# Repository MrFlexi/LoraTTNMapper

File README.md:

# LoraTTNMapper
Lora TTN Mapper

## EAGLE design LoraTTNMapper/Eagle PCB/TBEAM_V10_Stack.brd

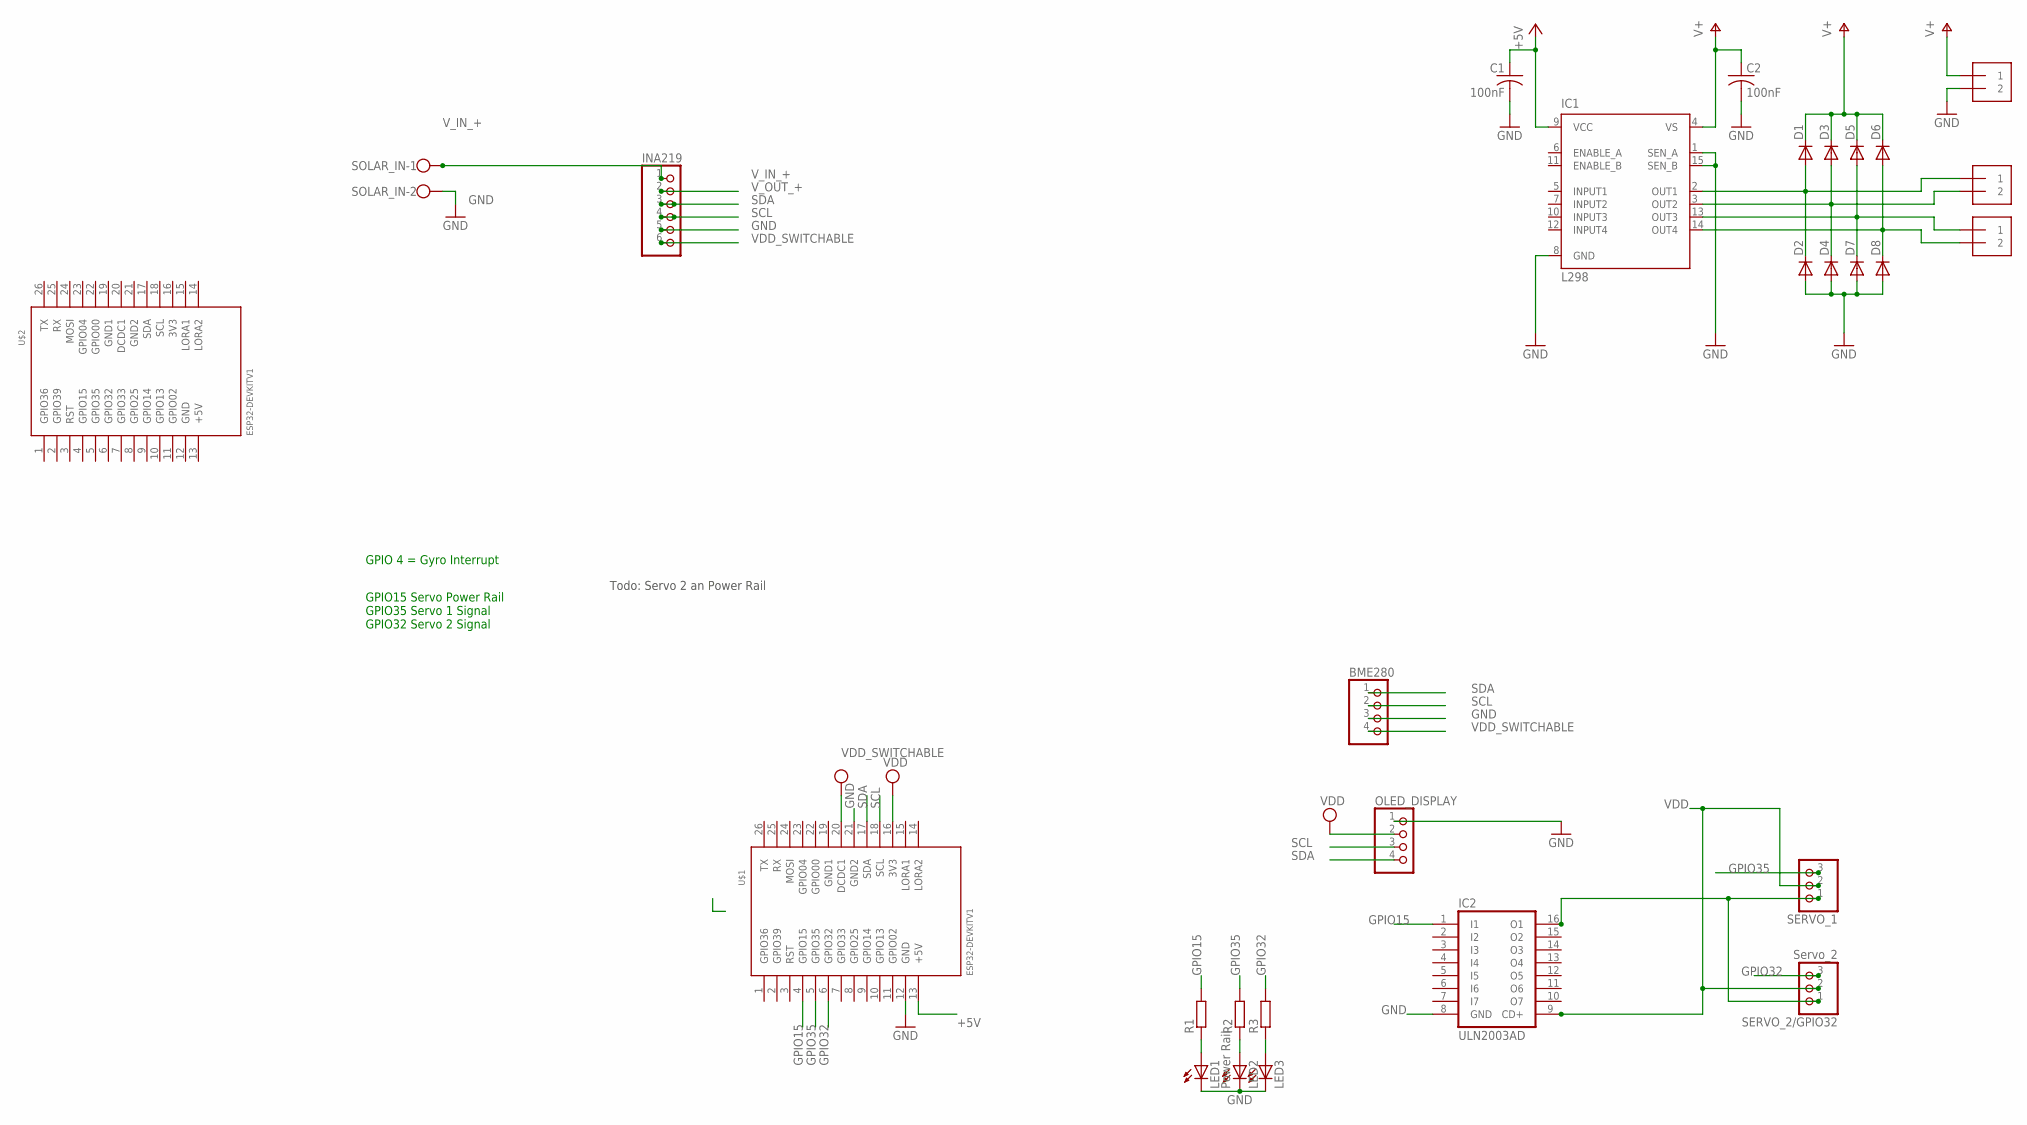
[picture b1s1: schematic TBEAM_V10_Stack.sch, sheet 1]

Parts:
BME280: PINHD-1X4; 1X04
C1, C2: 100nF; C050-024X044
D1, D2, D3, D4, D5, D6, D7, D8: DIODE-D-5; D-5
IC1: L298; MULTIWATT-15
IC2: ULN2003AD; SO16
INA219: PINHD-1X6; 1X06
J1, J2, J3: 1X2-3.5MM
LED1: Power Rail; SML1206
LED2, LED3: LEDSML1206; SML1206
OLED_DISPLAY: PINHD-1X4; 1X04
R1, R2, R3: R-EU_R1206; R1206
SERVO_1: PINHD-1X3; 1X03
SERVO_2/GPIO32: Servo_2; 1X03
SOLAR_IN: W237-102
U$1, U$2: ESP32DEVKITV1; ESP32-DEVKITV1

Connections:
+5V: C1.1, IC1.9 (VCC), U$1.13 (+5V)
GND: BME280.3, C1.2, C2.2, D2.A, D4.A, D7.A, D8.A, IC1.1 (SEN_A), IC1.8 (GND), IC1.15 (SEN_B), IC2.8 (GND), INA219.5, J1.2, LED1.C, LED2.C, LED3.C, OLED_DISPLAY.1, SOLAR_IN.2, U$1.12 (GND), U$1.21 (GND2)
GPIO15: IC2.1 (I1), R1.2, U$1.4 (GPIO15)
GPIO32: R3.2, SERVO_2/GPIO32.3, U$1.6 (GPIO32)
GPIO35: R2.2, SERVO_1.3, U$1.5 (GPIO35)
unnamed: IC2.16 (O1), SERVO_1.1, SERVO_2/GPIO32.1
unnamed: LED1.A, R1.1
unnamed: LED2.A, R2.1
unnamed: LED3.A, R3.1
unnamed: D1.A, D2.C, IC1.2 (OUT1), J2.1
unnamed: D3.A, D4.C, IC1.3 (OUT2), J2.2
unnamed: D6.A, D8.C, IC1.14 (OUT4), J3.2
unnamed: D5.A, D7.C, IC1.13 (OUT3), J3.1
SCL: BME280.2, INA219.4, OLED_DISPLAY.3, U$1.18 (SCL)
SDA: BME280.1, INA219.3, OLED_DISPLAY.4, U$1.17 (SDA)
V+: C2.1, D1.C, D3.C, D5.C, D6.C, IC1.4 (VS), J1.1
VDD: IC2.9 (CD+), OLED_DISPLAY.2, SERVO_1.2, SERVO_2/GPIO32.2, U$1.16 (3V3)
VDD_SWITCHABLE: BME280.4, INA219.6, U$1.20 (DCDC1)
V_IN_+: INA219.1, SOLAR_IN.1
V_OUT_+: INA219.2

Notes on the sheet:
GPIO15 Servo Power Rail GPIO35 Servo 1 Signal GPIO32 Servo 2 Signal
GPIO 4 = Gyro Interrupt
Todo: Servo 2 an Power Rail

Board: 2 copper layers, 29 parts (0 on the bottom side), 19 nets, no tracks yet.

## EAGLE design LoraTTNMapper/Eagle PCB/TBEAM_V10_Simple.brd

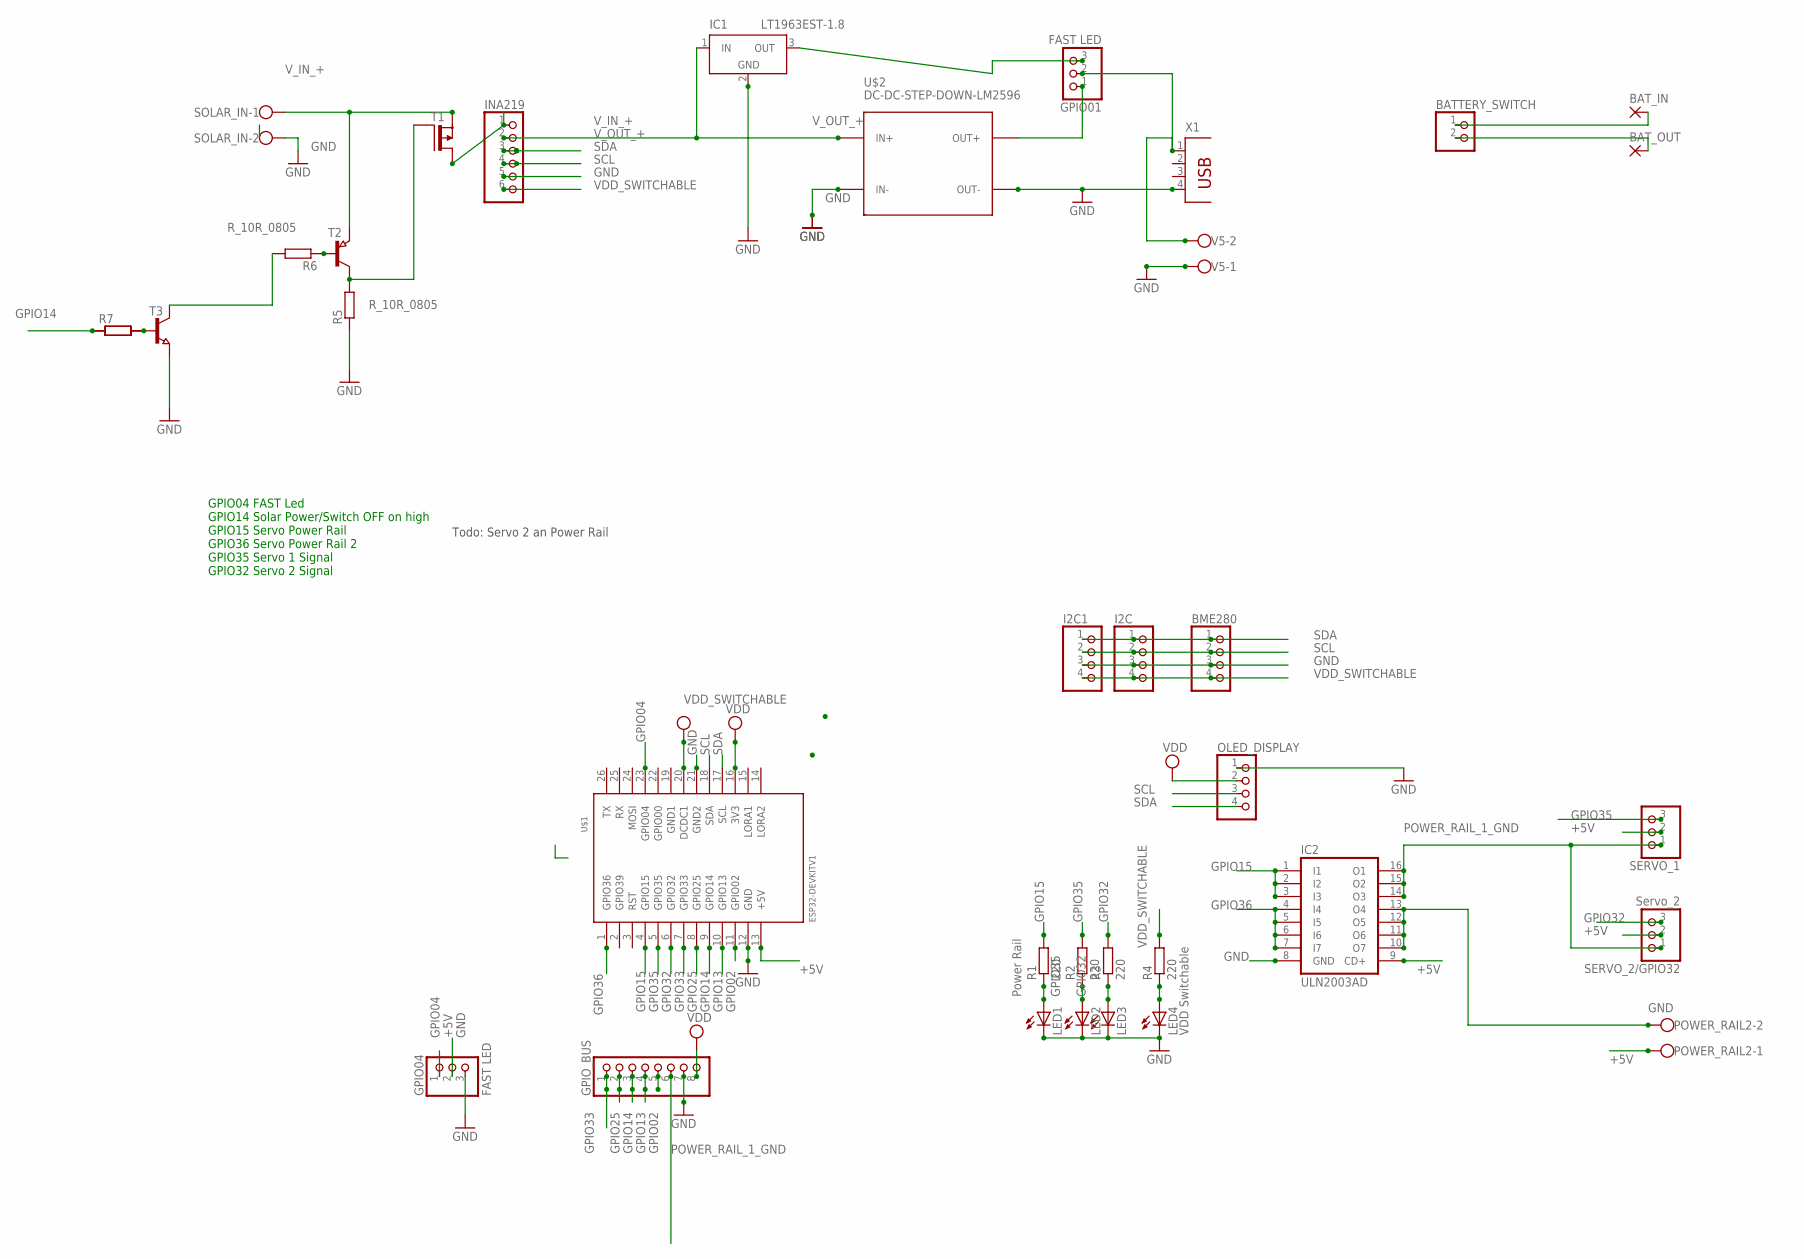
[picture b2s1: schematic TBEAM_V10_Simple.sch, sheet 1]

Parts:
BATTERY_SWITCH: PINHD-1X2; 1X02
BAT_IN: SMD5; SMD2,54-5,08
BAT_OUT: SMD5; SMD2,54-5,08
BME280: PINHD-1X4; 1X04
GPIO01, GPIO04: FAST LED; 1X03
GPIO_BUS: PINHD-1X8; 1X08
I2C, I2C1: PINHD-1X4; 1X04
IC1: LT1963EST-1.8; SOT223
IC2: ULN2003AD; SO16
INA219: PINHD-1X6; 1X06
LED1: Power Rail; SML1206
LED2: GPIO35; SML1206
LED3: GPIO32; SML1206
LED4: VDD Switchable; SML1206
OLED_DISPLAY: PINHD-1X4; 1X04
POWER_RAIL2: W237-102
R1, R2, R3, R4: 220; R1206
R5, R6: R_10R_0805; R0805
R7, R8: R_1.8K_0805; R0805
SERVO_1: PINHD-1X3; 1X03
SERVO_2/GPIO32: Servo_2; 1X03
SOLAR_IN: W237-102
T1: T_P-MOSFET_AO3401A_ALPHA_SOT23-GSD; SOT23
T2: T_PNP_SS8550-Y2_CHANGJ_SOT23-BEC; SOT23
T3: T_NPN_SS8050_CHANGJ_SOT23-BEC; SOT23
U$1: ESP32DEVKITV1; ESP32-DEVKITV1
U$2: DC-DC-STEP-DOWN-LM2596
V5: W237-102
X1: PN87520

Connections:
+5V: GPIO04.2, IC2.9 (CD+), POWER_RAIL2.1, SERVO_1.2, SERVO_2/GPIO32.2, U$1.13 (+5V)
BUCK-CONVERTER: GPIO01.1, U$2.OUT+
GND: BME280.3, GPIO04.3, GPIO_BUS.7, I2C.3, I2C1.3, IC1.2 (GND), IC1.4 (GND), IC2.8 (GND), INA219.5, LED1.C, LED2.C, LED3.C, LED4.C, OLED_DISPLAY.1, R5.1, SOLAR_IN.2, T3.2 (E), U$1.12 (GND), U$1.21 (GND2), U$2.IN-, U$2.OUT-, V5.1, X1.4
GPIO02: GPIO_BUS.5, U$1.11 (GPIO02)
GPIO04: GPIO04.1, U$1.23 (GPIO04)
GPIO13: GPIO_BUS.4, U$1.10 (GPIO13)
GPIO14: GPIO_BUS.3, R7.1, R8.1, U$1.9 (GPIO14)
GPIO15: IC2.1 (I1), IC2.2 (I2), IC2.3 (I3), R1.2, U$1.4 (GPIO15)
GPIO25: GPIO_BUS.2, U$1.8 (GPIO25)
GPIO32: R3.2, SERVO_2/GPIO32.3, U$1.6 (GPIO32)
GPIO33: GPIO_BUS.1, U$1.7 (GPIO33)
GPIO35: R2.2, SERVO_1.3, U$1.5 (GPIO35)
GPIO36: IC2.4 (I4), IC2.5 (I5), IC2.6 (I6), IC2.7 (I7), U$1.1 (GPIO36)
unnamed: LED1.A, R1.1
unnamed: LED2.A, R2.1
unnamed: LED3.A, R3.1
unnamed: GPIO01.2, V5.2, X1.1
unnamed: BATTERY_SWITCH.1, BAT_IN.1
unnamed: BATTERY_SWITCH.2, BAT_OUT.1
unnamed: LED4.A, R4.1
unnamed: IC2.10 (O7), IC2.11 (O6), IC2.12 (O5), IC2.13 (O4), POWER_RAIL2.2
unnamed: SOLAR_IN.1, T1.2 (S), T2.2 (E)
unnamed: GPIO01.3, IC1.3 (OUT)
unnamed: R5.2, T1.1 (G), T2.3 (C)
unnamed: R6.1, T2.1 (B)
unnamed: R6.2, T3.3 (C)
unnamed: R7.2, R8.2, T3.1 (B)
POWER_RAIL_1_GND: GPIO_BUS.6, IC2.14 (O3), IC2.15 (O2), IC2.16 (O1), SERVO_1.1, SERVO_2/GPIO32.1
SCL: BME280.2, I2C.2, I2C1.2, INA219.4, OLED_DISPLAY.3, U$1.18 (SDA)
SDA: BME280.1, I2C.1, I2C1.1, INA219.3, OLED_DISPLAY.4, U$1.17 (SCL)
VDD: GPIO_BUS.8, OLED_DISPLAY.2, U$1.16 (3V3)
VDD_SWITCHABLE: BME280.4, I2C.4, I2C1.4, INA219.6, R4.2, U$1.20 (DCDC1)
V_IN_+: INA219.1, T1.3 (D)
V_OUT_+: IC1.1 (IN), INA219.2, U$2.IN+

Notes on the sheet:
GPIO04 FAST Led GPIO14 Solar Power/Switch OFF on high GPIO15 Servo Power Rail GPIO36 Servo Power Rail 2 GPIO35 Servo 1 Signal GPIO32 Servo 2 Signal
Todo: Servo 2 an Power Rail

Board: 2 copper layers, 36 parts (3 on the bottom side), 34 nets, no tracks yet.

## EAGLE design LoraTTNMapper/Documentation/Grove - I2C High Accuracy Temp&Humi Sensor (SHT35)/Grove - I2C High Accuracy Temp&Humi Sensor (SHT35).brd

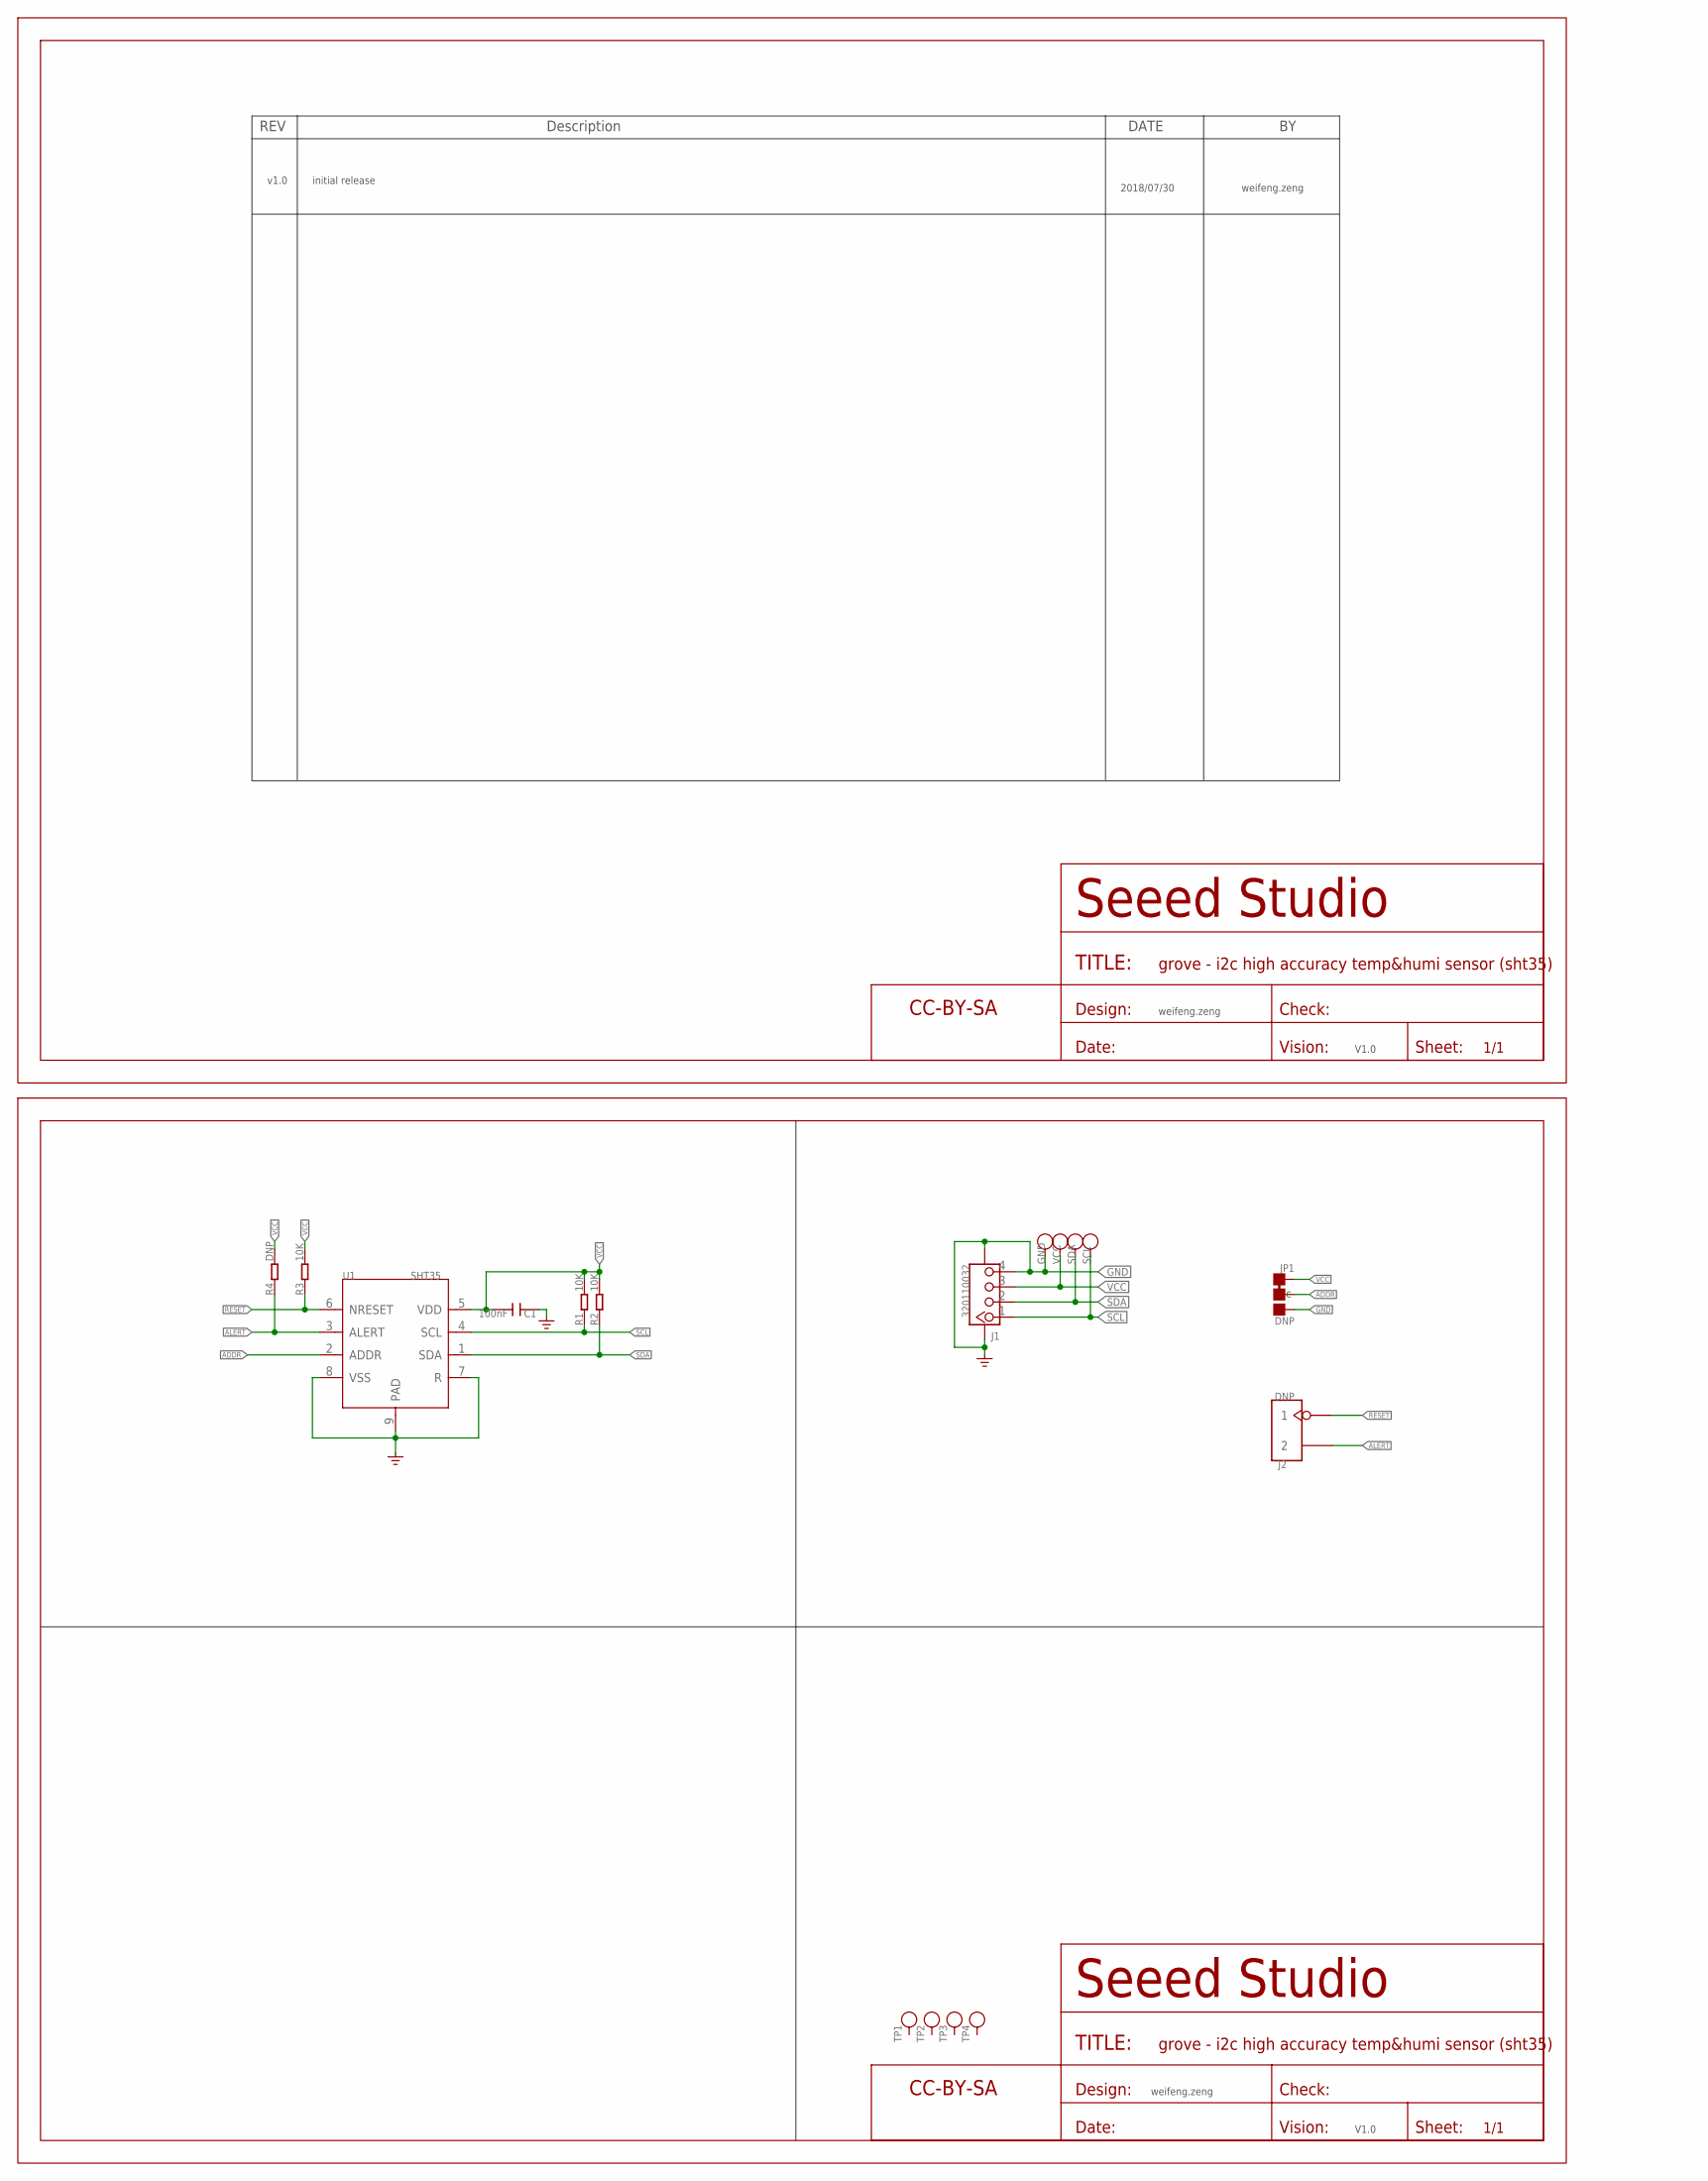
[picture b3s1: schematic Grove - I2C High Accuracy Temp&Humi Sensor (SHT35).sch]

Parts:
C1: 100nF; C0603
FR1, FR2: SEEEDSTUDIO-OPEN-SCH-FRAME; SEEEDSTUDIO-PCB-FRAME
GND: TEST-POINT'4545'; TP-D45MIL
J1: 320110032; HW4-SMD-2.0-90D
J2: DNP; H2-2.54
JP1: DNP; 3P-SMD-SHORT
R1, R2, R3: 10K; R0603
R4: DNP; R0603
SCL: TEST-POINT'4545'; TP-D45MIL
SDA: TEST-POINT'4545'; TP-D45MIL
TP1, TP2, TP3, TP4: TEST-POINT'4545'; TP-D45MIL
U1: SHT35; DFN8-0.5-2.5X2.5MM
VCC: TEST-POINT'4545'; TP-D45MIL

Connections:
ADDR: JP1.MM (C), U1.2 (ADDR)
ALERT: J2.2, R4.1, U1.3 (ALERT)
GND: C1.2, GND.T, J1.4, J1.SS1, J1.SS2, JP1.00 (R), U1.7 (R), U1.8 (VSS), U1.9 (PAD)
RESET: J2.1, R3.1, U1.6 (NRESET)
SCL: J1.1, R1.1, SCL.T, U1.4 (SCL)
SDA: J1.2, R2.1, SDA.T, U1.1 (SDA)
VCC: C1.1, J1.3, JP1.11 (L), R1.2, R2.2, R3.2, R4.2, U1.5 (VDD), VCC.T

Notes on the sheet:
v1.0
initial release
2018/07/30
weifeng.zeng
V1.0

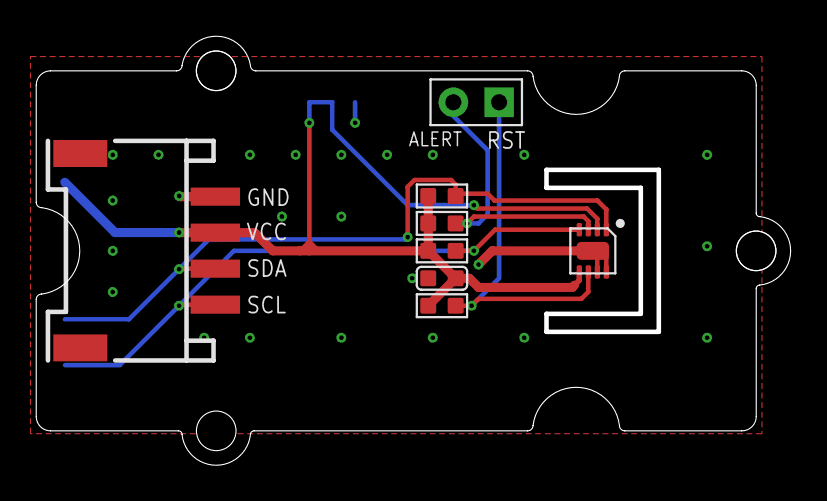
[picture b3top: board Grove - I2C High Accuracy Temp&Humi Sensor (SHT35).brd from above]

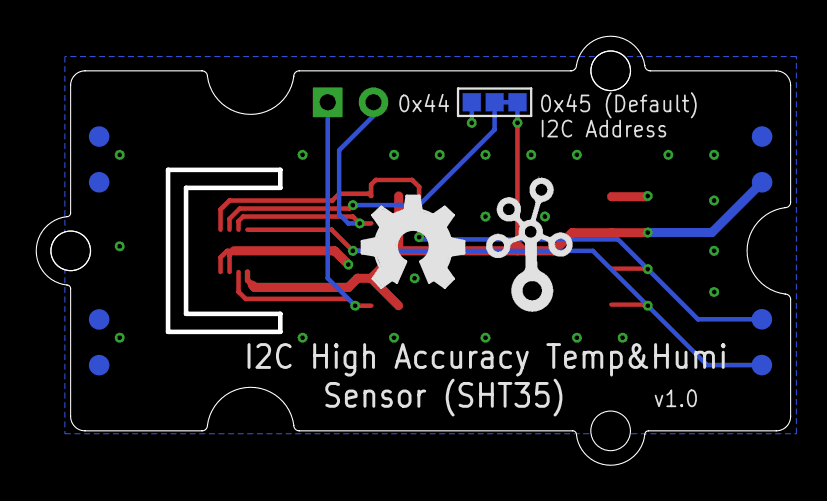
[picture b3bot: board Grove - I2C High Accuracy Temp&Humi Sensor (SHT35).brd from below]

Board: 2 copper layers, 41.9 x 23.8 mm, 22 parts (11 on the bottom side), 7 nets.

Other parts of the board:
U10: GROVE-TEST-PLATFORM
U$3: OSHW_FILLX200_NOTEXT
U$4: TWIGLOGO

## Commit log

2019-09-01 Init
2019-09-01 kein Display
2019-09-02 New TTN App
2019-09-06 T-Beam V1.0 with Power Managament Unit burned after unknown issue
2019-09-06 T-Beam Schematics and APX192 Datasheet added
2019-09-10 code sanitation
2019-09-11 code sanitation II
2019-09-11 Data Buffer included
2019-09-12 Now it compiles...
2019-09-12 Version 1.0
2019-09-12 Data Inbound
2019-09-12 Timing to be updated
2019-09-12 Power Management Includes copied
2019-09-12 Battery measurement included
2019-09-16 Display and deep sleep
2019-09-21 GPS low power mode
2019-09-25 Dashboard
2019-10-04 MQTT Included
2019-10-20 Compiles, but display errors AXP not O.K
2019-10-20 fast fertig
2019-10-21 Jipiii
2019-10-23 GPS code cleanup
2019-10-23 5 Min Deep Sleep
2019-10-23 Soft sleep / always on
2019-10-27 SolarPanel
2019-10-29 Message Queue In o.k.
2019-11-07 Button to switch display
2019-11-09 Lora send queue
2019-11-10 no gps fix
2019-11-11 Integration LPP Cayenne
2019-11-11 na ja
2019-11-12 GPS reset deleted
2019-11-12 BAT Voltage
2019-11-12 MQTT code cleanup
2019-11-14 lora.h
2019-11-14 lora h end
2019-11-14 Lora GPS
2019-11-14 GPS to Cayenne
2019-11-14 comments added
2019-11-16 LPP GPS fixed
2019-11-17 Queue Bug Fixig
2019-11-17 dodeel
2019-11-18 Improved queue handling
2019-11-18 Queue cleansing
2019-11-20 OTA Update
2019-11-20 OTA now its o.k.
2019-11-20 success
2019-11-21 Replace Ug2 lib by ss_oled
2019-11-21 DeepSleep ON
2019-11-23 all on
2019-11-23 V2.0
2019-11-23 jetzt klappt es
2019-11-25 ssisi
2019-11-25 Wifi Conditional off
2019-11-25 WIFI Optimization
2019-11-25 V2.3
2019-11-25 Display Update
2019-11-26 5 to 5
2019-11-26 LORA Firmware Version
2019-12-02 Sleep Off 2.6
2019-12-05 BLE Support
2019-12-05 BLE, no memory
2019-12-05 BLE OFF
2019-12-05 Flash Partition changed, minimal SPIFF
2019-12-06 Display Page Settings
2019-12-06 es geht
2019-12-18 Downgrade TBEAM V07
2019-12-18 down again
2019-12-18 down ok
2019-12-19 down
2019-12-19 some fixes in OTA
2019-12-19 micro spiffs
2019-12-19 more info
2019-12-19 tata
2019-12-20 displa defect
2019-12-25 Display Runmode = 0
2019-12-25 new start
2019-12-30 Downgrade V07 + Display O.K.
2019-12-30 Displav move O.K.
2020-01-08 Mini Spiff
2020-01-08 Min Spiff
2020-01-08 SOme enhancements V4.0
2020-01-08 small enhancement
2020-01-08 V1.0 Init
2020-01-08 Power On/Off Button
2020-01-08 Sleep On, OTA On
2020-01-08 30 Min Sleep
2020-01-09 minimal adjustments
2020-01-11 Deep Sleep / Power IRQ
2020-01-12 ADXL345
2020-01-13 ADXL burst read
2020-01-13 ADXL Event
2020-01-14 ADXL dump
2020-01-14 IRQ changes
2020-01-17 desplay error
2020-01-20 Display O.K.
2020-01-20 Dislay OK
2020-01-20 delays in startup routine --> no dumps
2020-01-22 RX Data: RSSi und RSI im Display
2020-01-22 Serial BT
2020-01-23 BLE Included
2020-01-23 2 BLE Services
2020-01-23 Bluethooth on
2020-01-23 docu
2020-01-25 Improvements
2020-01-26 GPIO 00 Interrupt ON
2020-01-26 ADXL does not trigger INT1
2020-01-27 Profont 12 TR ADXL Interrupt LOW Modules on display
2020-01-27 ADXL INT experimente
2020-01-28 Only Port 2 Messages, Timing changed
2020-01-28 Lora Queue optimization
2020-01-28 Payload O.K.
2020-01-28 High Low Prio MSG
2020-01-29 Payload ist nun schön
2020-01-29 Jipii
2020-01-31 Eagle PCB
2020-02-01 LORA PCB
2020-02-02 Gyro + PCB
2020-02-03 Gyro
2020-02-03 fast O.K.
2020-02-05 Integration Webserver
2020-02-05 Erster Test
2020-02-05 sap_ui_core js moved
2020-02-05 bug fixes
2020-02-05 fixes
2020-02-05 files
2020-02-05 now it works
2020-02-05 es läuft
2020-02-06 Webserver: Battery Status
2020-02-06 Websocket fixes
2020-02-06 New Index HTML
2020-02-07 O.K.
2020-02-08 webserver O.K. Queue handling optimized
2020-02-10 Websocket Send
2020-02-10 WebSocket
2020-02-10 Webserver stable
2020-02-15 no it compiles again
2020-02-17 Revert "Merge branch 'development' of https://github.com/MrFlexi/LoraTTNMapper into development"
    This reverts commit 1267d348112a162c1f969a7523d3d6c11075ca5c, reversing
    changes made to 49d0e219701fe1a610e9a39d542b0d4ab6c21bf8.
2020-02-18 Led Init
2020-02-18 GyrosKope
2020-02-19 Gyro without dumps
2020-02-19 Gyro Events via RTOS
2020-02-20 Global Interrupt Register
2020-02-20 Potentiometer
2020-02-20 Poti
2020-02-20 alles gut
2020-02-21 viele kleine Verbesserungen
2020-02-23 Stable for 24h
2020-02-26 RTOS Poti
2020-02-26 ADC RTOS
2020-02-26 ADC ready
2020-02-26 adc map
2020-02-27 LED rtos LOOP
2020-02-28 APX202 updated manually
2020-02-29 pmu mutex changes start
2020-03-02 Montag morgen
2020-03-03 Coulomb Register Read
2020-03-03 Library Included
2020-03-03 Coulomb counter O.K.
2020-03-03 spelling error
2020-03-04 Enable Coulomb Counter
2020-03-04 TTN remote command sleep + reset coulomb counter
2020-03-04 Small fixes
2020-03-08 Deepsleep 25
2020-04-04 Code clean up / #ifdef webcocket / PMU IRG Off
2020-04-05 Cayenne reset Coulomb Counter
2020-05-16 So long so good
2020-05-17 delays removed
2020-05-17 Boot sequence changed Gyrowith less dumps on init
2020-05-17 Device abstraction layer
2020-05-26 JS Utilities Library included
2020-06-04 Device ID 02 O.K.
2020-06-04 Wire.setClock(400000);
2020-06-13 Button handling
2020-07-07 BLE Scanner
2020-07-15 RTOS BLE Scanner
2020-07-15 bugfix
2020-08-16 Cayenne GPS
2020-09-27 Corona Off
2020-10-08 jaja
2020-10-08 #HAS LORA
2020-10-08 Mqtt does not compile
2020-10-08 yes it compiles
2020-10-08 jetzt
2020-10-08 this works...
2020-10-11 V1.0
2020-10-11 CPU Temperature included
2020-10-14 weniger i2c dumps
2020-10-15 MQTT Command
2020-10-15 Webserver ON
2020-10-15 Save settings
2020-10-16 only one mqtt connection possible
2020-10-17 MQTT Device ID
2020-10-20 jojo
2020-10-22 Enable watchdog timer 3 s
2020-10-22 Mqtt Comand
2020-10-22 Umstellung Settings auf SPIFF
2020-10-26 ota on
2020-10-26 fertisch
2020-10-28 all PMU Interrupt off
2020-10-28 Code cleanup
2020-10-28 Remote debugging
2020-10-28 und noch etwas
2020-10-30 better power
2020-10-31 wdt timeout
2020-10-31 Stable
2020-11-07 BLE+GYRO+DASH removed
2020-11-11 so so
2020-11-12 ina219 included
2020-11-19 Klappt
2020-11-23 payload optimization
2020-11-23 better
2020-12-11 increase spleep time if bat low
2021-02-23 set sleep time
2021-03-25 BAT sleep timer
2021-05-05 deep sllep adjusted
2021-05-16 Better power management
2021-06-11 Migration to TTN V3
2021-06-16 Board Layout
2021-06-16 tbeam-02 migrated to TTN V3
2021-06-22 MQTT
2021-06-25 set charge controll
2021-06-29 INA219
2021-07-22 pcb layout
2021-07-22 gps latitude > 0 to fix values in ttn
2021-10-15 Device names chanched to mrflexi-xx
2021-10-16 better Fiori
2021-10-23 toJson
2021-10-23 New Launchad Tiles
2021-11-01 Documentation
2021-11-09 Ports O.K.
2021-11-18 TrainControll-Start
2022-03-04 UI5 improved
2022-03-04 UI5 with Panels
2022-03-08 Soil Sensor
2022-03-08 soso
2022-03-17 Temp + Hum via Lora
2022-03-18 better Poti
2022-03-19 TTGO Camera
2022-03-25 Soil Moisture
2022-03-28 New MQTT
2022-04-03 HCSR04
2022-04-10 fast gut
2022-04-15 Camera and TFT
2022-04-20 PWM Servo
2022-04-21 MQTT Servo
2022-04-21 Time server
2022-04-21 SunPos calculation
2022-05-05 Sun Calc
2022-05-09 Sun Eleveation via BLE
2022-06-21 New Payload formats
2022-06-24 new payload format
2022-07-13 bisl besser
2022-08-06 Upgrade Espressif Framework
2022-08-06 Espressif downgrade to version 3.5.0
2022-08-10 New Startup Icons
2022-08-11 Time fixes
2022-11-28 SunTracker
2022-12-15 SunPos.h removed
2023-01-16 cet + 1
2023-02-02 Bintray removed
2023-02-10 PMU sleep mode switch off all
2023-02-10 compiles Ok
2023-02-24 klappt nicht
2023-03-03 SunTracker TTGOV2
2023-03-05 gut so
2023-03-05 New Fiori Tiles Coulomb
2023-03-11 MPP Tracker
2023-03-12 Init OK
2023-03-16 Charge Controller
2023-03-17 läuft
2023-03-26 Init OTA
2023-04-04 OTA display
2023-04-10 power management bug fix
2023-04-10 PCB Update P Mosfet to switch Solar Panel
2023-05-21 Servo + Ina219
2023-05-21 servo lib enhancements
2023-08-02 OpenSprinkler
2024-02-23 MPU6050 integrated
2024-02-23 Test
2024-02-23 WebSocket mit MPU6050
2024-02-23 Lidar VL53L1X included
2024-02-23 Py to visualize distances
2024-02-24 radar
2024-03-03 Init FlightControl
2024-03-04 to be revised
2024-03-04 three.js integration
2024-03-04 Flask
2024-03-04 FLASK MPU
2024-03-05 nice
2024-03-05 Websocket + FS data
2024-03-07 ESP OK
2024-03-16 Compass Gauge
2024-03-29 gitignore
2024-03-29 schmall improvements
2024-08-02 Bump vite from 5.1.4 to 5.1.7 in /LoraTTNMapper
    Bumps [vite](https://github.com/vitejs/vite/tree/HEAD/packages/vite) from 5.1.4 to 5.1.7.
    - [Release notes](https://github.com/vitejs/vite/releases)
    - [Changelog](https://github.com/vitejs/vite/blob/v5.1.7/packages/vite/CHANGELOG.md)
    - [Commits](https://github.com/vitejs/vite/commits/v5.1.7/packages/vite)
    ---
    updated-dependencies:
2024-08-02 Revert "hh"
    This reverts commit fce6bef452cdaf3a00de99f54c58dd2c15105be7.
2024-08-02 Reapply "hh"
    This reverts commit c2bd82fe4338d01305c2d4a28c05837331877a58.
2024-08-02 Revert "all together"
    This reverts commit ff2190918a2b624d5a6e0930ac74e8f9eef4c639, reversing
    changes made to dcd97c0a98cdba61bc365bd637e25b5b843a4e84.
2024-08-02 Compile O.K.
2024-08-04 Wifi Counter
2024-08-04 mac list ok
2024-08-04 lets check
2024-08-05 file handlink not OK
2024-08-06 switch from json to array
2024-08-10 wifi defekt
2024-08-10 Wifi Ok again
2024-08-13 new rtos task include
2024-08-26 MacList by Date
2024-08-30 Multi Download does not work yet

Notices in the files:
parts and their libraries:
moudle-new: This work is licensed under the Creative Commons Attribution 4.0 International License.
To view a copy of this license,visit:
http://creativecommons.org/licenses/by-sa/4.0
moudle-new: CC-BY-SA
